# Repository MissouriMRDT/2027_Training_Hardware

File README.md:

# Training Hardware
Please follow along with the KiCAD trainings found [here](https://mailmissouri.sharepoint.com/sites/SDELC-MarsRoverDesignTeam-Ogrp/Shared%20Documents/Forms/AllItems.aspx?id=%2Fsites%2FSDELC%2DMarsRoverDesignTeam%2DOgrp%2FShared%20Documents%2F%23ROVESODRIVE%2F2027%20%28KICKFLIP%29%2F2%20%2D%20Arch%20Electrical%2FResources&viewid=222fe0bf%2D5a43%2D4286%2Daf58%2Dd0eeca5d2865&FolderCTID=0x012000D37049AE53A0094484D716DAB5E334B6)

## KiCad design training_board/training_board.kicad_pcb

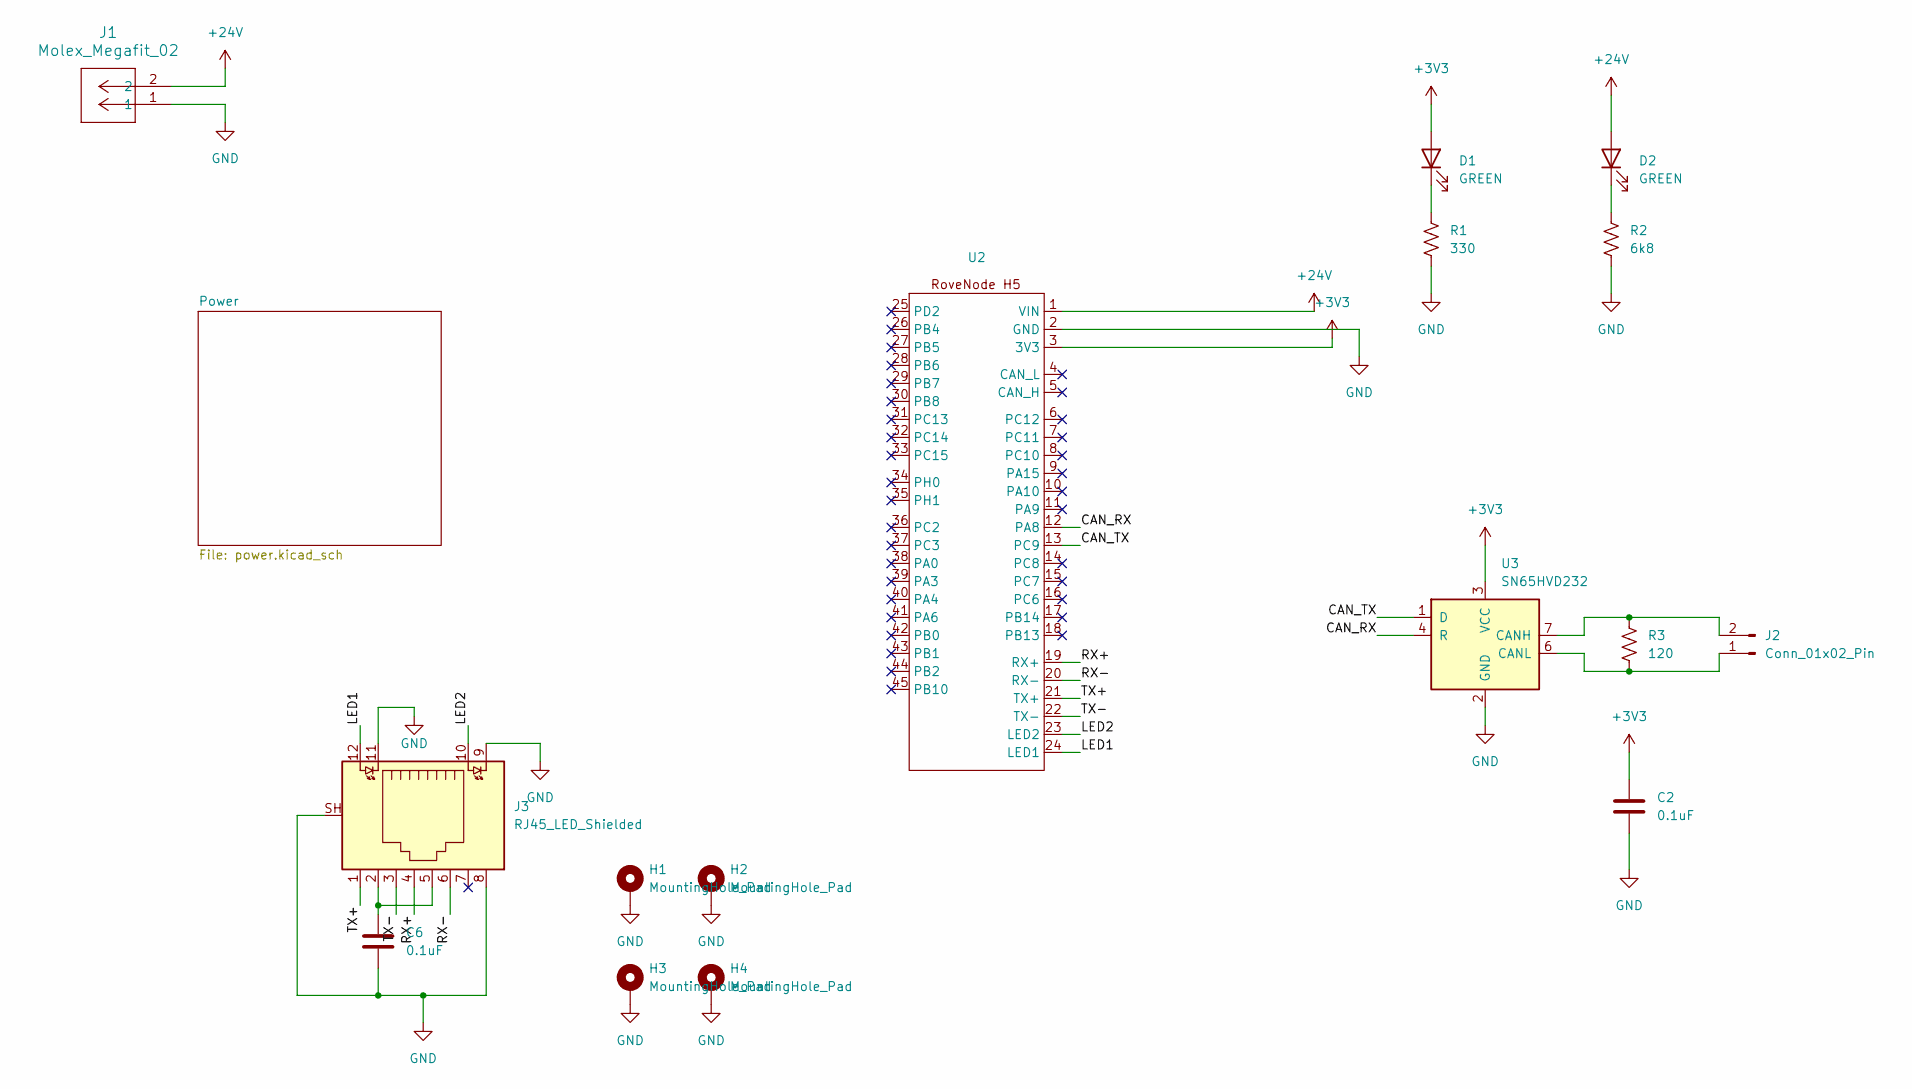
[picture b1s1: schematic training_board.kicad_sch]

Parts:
C2, C6: 0.1uF; C_0603_1608Metric_Pad1.08x0.95mm_HandSolder
D1, D2: GREEN; D_0603_1608Metric
H1, H2, H3, H4: MountingHole_Pad; 4_40_Hole_Pad_Via
J1: Molex_Megafit_02; MOLEX_MegaFit_02_Horizontal
J2: Conn_01x02_Pin; JST_PH_S2B-PH-SM4-TB_1x02-1MP_P2.00mm_Horizontal
J3: RJ45_LED_Shielded; RJ45_Teensy
R1: 330; R_0603_1608Metric_Pad0.98x0.95mm_HandSolder
R2: 6k8; R_0603_1608Metric_Pad0.98x0.95mm_HandSolder
R3: 120; R_0603_1608Metric_Pad0.98x0.95mm_HandSolder
U2: RoveNode_H5
U3: SN65HVD232; SOIC-8_3.9x4.9mm_P1.27mm

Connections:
+3V3: C2.1, D1.2 (A), U2.3 (3V3), U3.3 (VCC); also elsewhere on the board
+24V: D2.2 (A), J1.2, U2.1 (VIN); also elsewhere on the board
/CAN_RX: U2.12 (PA8), U3.4 (R)
/CAN_TX: U2.13 (PC9), U3.1 (D)
/LED1: J3.12, U2.24 (LED1)
/LED2: J3.10, U2.23 (LED2)
/RX+: J3.4, U2.19 (RX+)
/RX-: J3.6, U2.20 (RX-)
/TX+: J3.1, U2.21 (TX+)
/TX-: J3.3, U2.22 (TX-)
GND: C2.2, C6.2, H1.1 (1_1), H2.1 (1_1), H3.1 (1_1), H4.1 (1_1), J1.1, J3.8, J3.9, J3.11, J3.SH, R1.2, R2.2, U2.2 (GND), U3.2 (GND); also elsewhere on the board
unnamed: C6.1, J3.2, J3.5
unnamed: D1.1 (K), R1.1
unnamed: D2.1 (K), R2.1
unnamed: J2.1, R3.2, U3.6 (CANL)
unnamed: J2.2, R3.1, U3.7 (CANH)

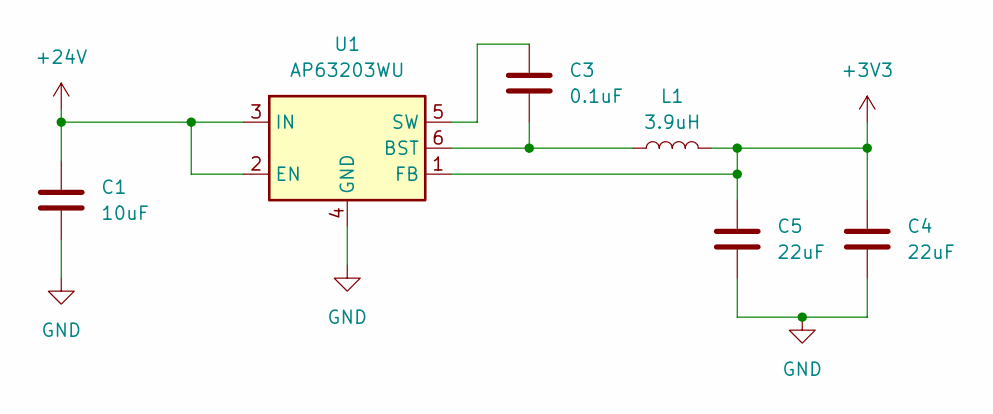
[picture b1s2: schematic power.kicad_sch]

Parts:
C1: 10uF; C_0603_1608Metric_Pad1.08x0.95mm_HandSolder
C3: 0.1uF; C_0603_1608Metric_Pad1.08x0.95mm_HandSolder
C4, C5: 22uF; C_0603_1608Metric_Pad1.08x0.95mm_HandSolder
L1: 3.9uH; L_1008_2520Metric_Pad1.43x2.20mm_HandSolder
U1: AP63203WU; TSOT-23-6

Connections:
+3V3: C4.1, C5.1, L1.2, U1.1 (FB); also elsewhere on the board
+24V: C1.1, U1.2 (EN), U1.3 (IN); also elsewhere on the board
GND: C1.2, C4.2, C5.2, U1.4 (GND); also elsewhere on the board
unnamed: C3.2, L1.1, U1.6 (BST)
unnamed: C3.1, U1.5 (SW)

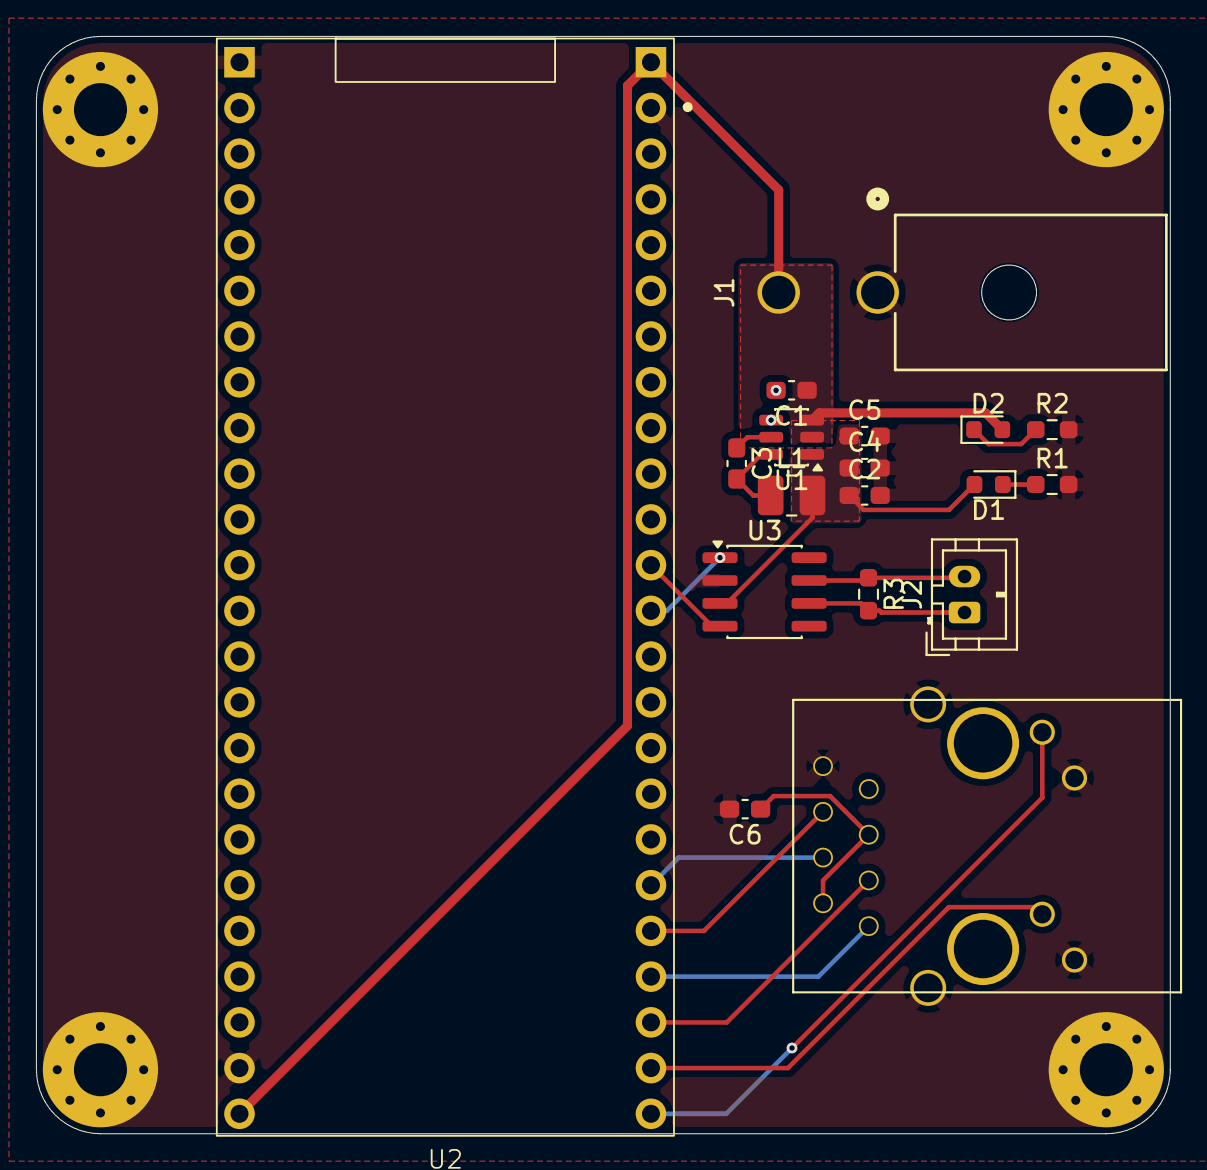
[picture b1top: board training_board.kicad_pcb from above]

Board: 2 copper layers, 63.0 x 61.0 mm, 22 parts (0 on the bottom side), 18 nets.
